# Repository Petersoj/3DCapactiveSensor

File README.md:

# 3DCapacitiveSensor

This project uses the STM32F072RB MCU on the 32F072BDISCOVERY board and a large "3D" capacitor to measure the XYZ coordinates of a user's hand in physical space so that a user can move/click a computer mouse without touching anything. This project was inspired by [this](https://www.youtube.com/watch?v=ikD_3Vemkf0) video.

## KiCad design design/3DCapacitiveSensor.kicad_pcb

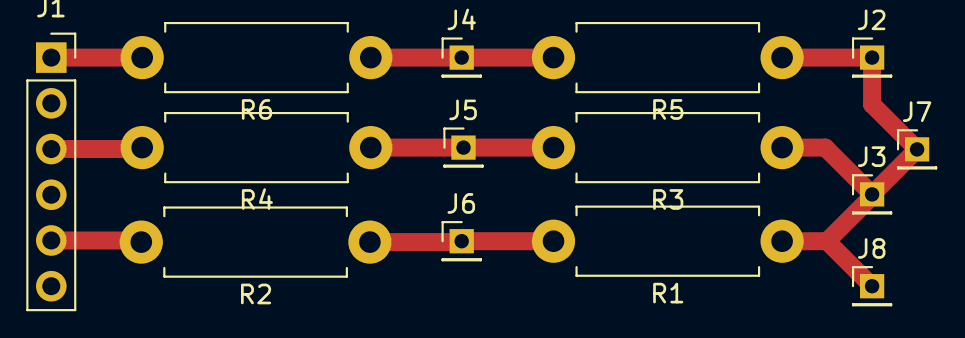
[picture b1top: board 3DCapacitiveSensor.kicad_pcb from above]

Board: 2 copper layers, 14 parts (0 on the bottom side), 7 nets.

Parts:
J1: Pin Socket; PinSocket_1x06_P2.54mm_Vertical
J2: X_shield; PinHeader_1x01_P2.00mm_Vertical
J3: Y_shield; PinHeader_1x01_P2.00mm_Vertical
J4: X_plate; PinHeader_1x01_P2.00mm_Vertical
J5: Y_plate; PinHeader_1x01_P2.00mm_Vertical
J6: Z_plate; PinHeader_1x01_P2.00mm_Vertical
J7: 3V; PinHeader_1x01_P2.00mm_Vertical
J8: Z_shield; PinHeader_1x01_P2.00mm_Vertical
R1, R3, R5: 220K; R_Axial_DIN0411_L9.9mm_D3.6mm_P12.70mm_Horizontal
R2, R4, R6: 10K; R_Axial_DIN0411_L9.9mm_D3.6mm_P12.70mm_Horizontal

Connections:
/X_pin: J1.1, R6.2
/Y_pin: J1.3, R4.2
/Z_pin: J1.5, R2.2
/shield_wire: J2.1, J3.1, J7.1, J8.1, R1.1, R3.1, R5.1
unnamed: J4.1, R5.2, R6.1
unnamed: J5.1, R3.2, R4.1
unnamed: J6.1, R1.2, R2.1

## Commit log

2021-04-10 Add README
2021-04-10 Add schematic and board layout
2021-04-11 Add Visual Studio client project
2021-04-15 Add initial uVision project for STM32 DiscoveryBoard
2021-04-15 Add initial testing code for UART communication
2021-04-27 Reformat and refactor client solution and add new projects
2021-04-27 Modify gitignore
2021-04-30 clang-format LLVM style source
2021-04-30 Reformat and add bit logic methods
2021-04-30 Add SerialInterface
2021-04-30 Update client view, reconfigure solution, create SerialInterface
2021-04-30 Finish CursorController implementation
2021-04-30 Link up handlers/delegates and organize
2021-04-30 Finish implementation of Controller and such
2021-05-01 Update schematic
2021-05-01 Add configure_usart3 and itoa functions
2021-05-01 Add usart3 TX, configure rcc, and adc/gpio functions
2021-05-01 Add function prototypes and add ADC wait mode
2021-05-01 Fix ADC function bugs and add testing code
2021-05-01 Get channels PA0, PA4, and PA5 working.
2021-05-02 Replace counting from ADC to Schmitt trigger GPIO
2021-05-02 Use timer peripheral for capacitance level counting
2021-05-03 Revert to GPIO counting (can't get timer peripheral working)
2021-05-03 Modify serial data format (X plate capacitor works now)
2021-05-04 Change clock frequency from 8MHz to 48MHz for greater resolution
2021-05-04 Add motor driver code from Lab 7 and adapt it for x-plate speed control
